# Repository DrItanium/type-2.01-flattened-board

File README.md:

This project is a flattening of my i960 Eurocard Bus design into a mini itx
motherboard. The idea is that by leveraging the mini-itx/atx ecosystem I will
save a bunch of money. In this design, the chipset is an adafruit grand central
m4 with ram being provided by a file on an SD card (dedicated SD channel +
an effective cache implementation works wonders to hide nearly all latency).

The grand central m4 is exposed out the io shield area. You will see the
evolution of many ideas and where it started from as well. 

I have two 4809 microcontrollers on board as well. They are titled ME and PIC. 

ME or Management Engine abstracts the details of how one handles memory
transactions made by the i960. It generates the 20MHz clock and runs in lock
step with the i960Sx as well. The chipset (GCM4) interacts with the ME to
satisfy these requests. The communication protocol between chipset and ME is
designed to allow the chipset to run completely independently of the ME without
running too fast or out of sync. The ME also uses its CCLs to reduce the number
of ICs required. This includes:

- Enabling data lines on request by chipset
- Fail signal detection (externally synchronized)
- Ready signal detection with external override
- Controlling the i960 reset line (Chipset, ME, and PIC all have to be ready
		before i960 is pulled out of reset). Pullups and an external inverter
		are used to make sure that the i960 will stay in reset until everything is
		ready. 

PIC or Programmable Interrupt Controller makes sure that one can invoke any of
the four exposed interrupt lines by the i960Sx in a consistent manner. A serial
communication channel is provided to allow the chipset to configure the PIC.
The general idea is that each CCL of the PIC is devoted to a separate interrupt
line. The first three interrupts (~INT0, INT1, INT2) are meant for dedicated
interrupts within the i960. The third interrupt (~INT3) is the lowest priority
and designed for the chipset. When the chipset needs to interrupt the i960, it
sends an ~INT3. This causes the i960 to query the chipset what kind of
interrupt it was (through MMIO) and then send an IAC message to trigger an
internal interrupt. 

The PIC has peripherals like timers and such that can be connected to the CCLs
to trigger interrupts. The chipset talks with the PIC through the serial
connection to setup these options via the event system.

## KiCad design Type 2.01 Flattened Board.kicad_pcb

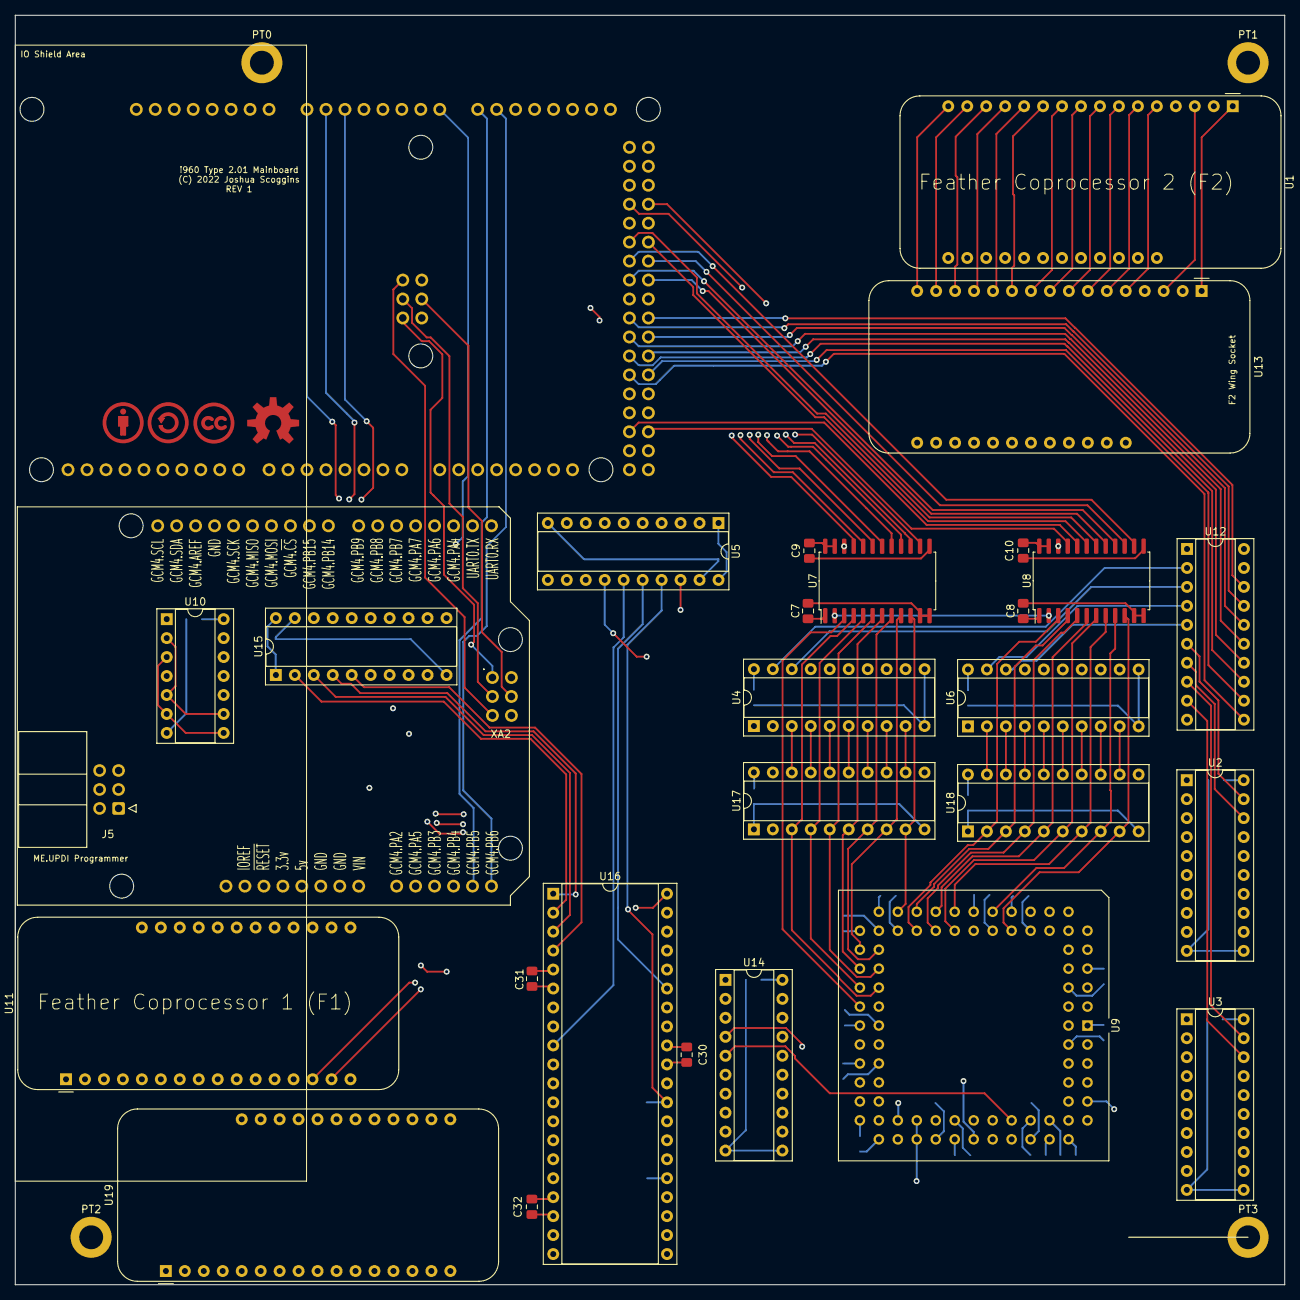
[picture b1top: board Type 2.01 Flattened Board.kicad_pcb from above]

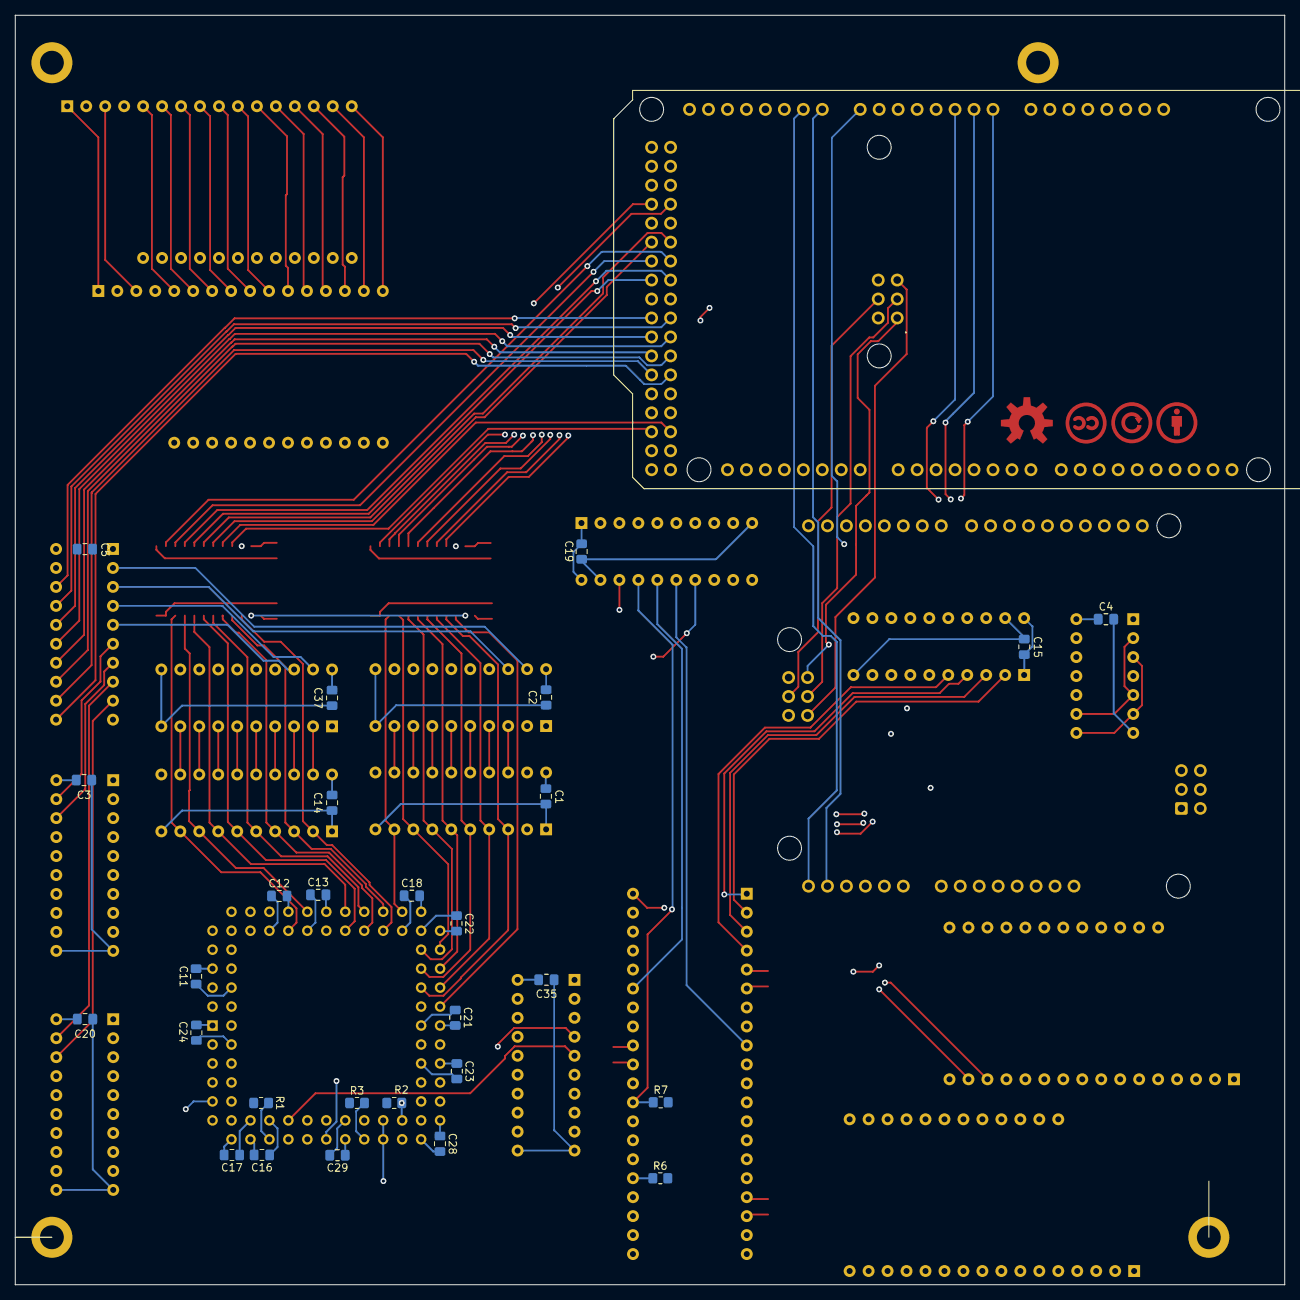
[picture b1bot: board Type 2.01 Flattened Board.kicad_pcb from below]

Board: 4 copper layers, 170.0 x 170.0 mm, 61 parts (29 on the bottom side), 209 nets.

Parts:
C1, C2, C3, C4, C5, C7, C8, C9, C10, C11, C12, C13, C14, C15, C16, C17, C18, C19, C20, C21, C22, C23, C24, C28, C29, C30, C31, C32, C35, C37: 0.1uF; C_0805_2012Metric_Pad1.18x1.45mm_HandSolder
J5: Conn_02x03_Odd_Even; IDC-Header_2x03_P2.54mm_Horizontal
PT0, PT1, PT2, PT3: MountingHole; MountingHole_3.2mm_M3_ISO14580_Pad
R1: 910; R_0805_2012Metric_Pad1.20x1.40mm_HandSolder
R2, R3, R6, R7: 10k; R_0805_2012Metric_Pad1.20x1.40mm_HandSolder
U1, U11, U13, U19: Adafruit_FeatherWing; Adafruit_Feather
U2, U3, U4, U6, U14: GAL16V8; DIP-20_W7.62mm_Socket
U5, U12, U15: 74AHC245; DIP-20_W7.62mm_Socket
U7, U8: 74LVC8T245; SOIC-24W_7.5x15.4mm_P1.27mm
U9: i960Sx_PLCC84; PLCC-84_THT-Socket
U10: 74AHC125; DIP-14_W7.62mm_Socket
U16: ATmega4809-PF; DIP-40_W15.24mm_Socket
U17, U18: 74AHC573; DIP-20_W7.62mm_Socket
XA1: Adafruit Grand Central M4; Arduino_Mega2560_Shield
XA2: Arduino_Uno_Shield

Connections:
+3.3V: U1.2 (3.3v), U1.28 (BAT), U11.2 (3.3v), U11.28 (BAT), U13.2 (3.3v), U13.28 (BAT), U19.2 (3.3v), U19.28 (BAT)
+3V3: XA1.3V3 (3.3V), XA2.3V3 (3.3V)
+5V: C1.1, C2.1, C3.1, C7.1, C8.1, C11.1, C12.1, C13.1, C14.1, C16.1, C17.1, C18.1, C19.1, C20.1, C21.1, C22.1, C23.1, C24.1, C28.1, C29.1, C30.1, C31.1, C32.1, C35.1, C37.1, J5.2, R1.2, R2.1, R3.1, R6.2, R7.2, U1.26 (USB), U2.20 (VCC), U3.20 (VCC), U4.20 (VCC), U5.1 (A->B), U5.20 (VCC), U6.20 (VCC), U7.1 (VCCA), U8.1 (VCCA), U9.1 (VCC), U9.6 (VCC), U9.17 (VCC), U9.21 (VCC), U9.31 (VCC), U9.33 (VCC), U9.44 (VCC), U9.47 (VCC), U9.53 (VCC), U9.62 (VCC), U9.71 (VCC), U9.73 (VCC), U11.26 (USB), U13.26 (USB), U14.20 (VCC), U16.5 (VCC), U16.17 (AVCC), U16.31 (VCC), U17.20 (VCC), U18.20 (VCC), U19.26 (USB), XA1.5V1 (5V), XA1.5V2 (SPI_5V), XA1.5V3 (5V), XA1.5V4 (5V), XA2.5V1 (5V), XA2.5V2 (SPI_5V)
/AREF: XA1.AREF, XA2.AREF
/BUS.PA2: XA1.A0, XA2.A0
/BUS.PA4: U1.10 (A5), U13.10 (A5), XA1.A13
/BUS.PA5: XA1.A1, XA2.A1
/BUS.PA6: U1.1 (~RESET), U13.1 (~RESET), XA1.A14
/BUS.PB2: U10.4, XA1.D9, XA2.D9
/BUS.PB3: XA1.A2, XA2.A2
/BUS.PB4: XA1.A7, XA2.A3
/BUS.PB5: XA1.A8, XA2.A4
/BUS.PB6: XA1.A9, XA2.A5
/BUS.PB7: U11.1 (~RESET), U19.1 (~RESET), XA1.A10
/BUS.PB8: U1.15 (TX), U13.15 (TX), XA1.A11
/BUS.PB9: U1.14 (RX), U13.14 (RX), XA1.A12
/BUS.PB18: U10.10, XA1.D8, XA2.D8
/BUS.PC18: XA1.D2 (D2_INT0), XA2.D2 (D2_INT0)
/BUS.PC19: XA1.D3 (D3_INT1), XA2.D3 (D3_INT1)
/BUS.PC20: XA1.D4, XA2.D4
/BUS.PC21: XA1.D5, XA2.D5
/BUS.PD20: XA1.D6, XA2.D6
/BUS.PD21: XA1.D7, XA2.D7
/DAZZLER.MISO: U10.2, U10.5, U10.9, XA2.D12
/Feather Copro0/Feather.A0: U11.5 (A0), U19.5 (A0)
/Feather Copro0/Feather.A1: U11.6 (A1), U19.6 (A1)
/Feather Copro0/Feather.A2: U11.7 (A2), U19.7 (A2)
/Feather Copro0/Feather.A3: U11.8 (A3), U19.8 (A3)
/Feather Copro0/Feather.A4: U11.9 (A4), U19.9 (A4)
/Feather Copro0/Feather.AREF: U11.3 (AREF), U19.3 (AREF)
/Feather Copro0/Feather.D5: U11.19 (D5), U19.19 (D5)
/Feather Copro0/Feather.D6: U11.20 (D6), U19.20 (D6)
/Feather Copro0/Feather.D9: U11.21 (D9), U19.21 (D9)
/Feather Copro0/Feather.D10: U11.22 (D10), U19.22 (D10)
/Feather Copro0/Feather.D11: U11.23 (D11), U19.23 (D11)
/Feather Copro0/Feather.D12: U11.24 (D12), U19.24 (D12)
/Feather Copro0/Feather.D13: U11.25 (D13), U19.25 (D13)
/Feather Copro0/Feather.EN: U11.27 (EN), U19.27 (EN)
/Feather Copro0/Feather.FREE: U11.16 (*), U19.16 (*)
/Feather Copro0/Feather.MISO: U11.13 (MISO), U19.13 (MISO)
/Feather Copro0/Feather.MOSI: U11.12 (MOSI), U19.12 (MOSI)
/Feather Copro0/Feather.SCK: U11.11 (SCK), U19.11 (SCK)
/Feather Copro0/Feather.SCL: U11.18 (SCL), U19.18 (SCL)
/Feather Copro0/Feather.SDA: U11.17 (SDA), U19.17 (SDA)
/Feather Copro1/Feather.A0: U1.5 (A0), U13.5 (A0)
/Feather Copro1/Feather.A1: U1.6 (A1), U13.6 (A1)
/Feather Copro1/Feather.A2: U1.7 (A2), U13.7 (A2)
/Feather Copro1/Feather.A3: U1.8 (A3), U13.8 (A3)
/Feather Copro1/Feather.A4: U1.9 (A4), U13.9 (A4)
/Feather Copro1/Feather.AREF: U1.3 (AREF), U13.3 (AREF)
/Feather Copro1/Feather.D5: U1.19 (D5), U13.19 (D5)
/Feather Copro1/Feather.D6: U1.20 (D6), U13.20 (D6)
/Feather Copro1/Feather.D9: U1.21 (D9), U13.21 (D9)
/Feather Copro1/Feather.D10: U1.22 (D10), U13.22 (D10)
/Feather Copro1/Feather.D11: U1.23 (D11), U13.23 (D11)
/Feather Copro1/Feather.D12: U1.24 (D12), U13.24 (D12)
/Feather Copro1/Feather.D13: U1.25 (D13), U13.25 (D13)
/Feather Copro1/Feather.EN: U1.27 (EN), U13.27 (EN)
/Feather Copro1/Feather.FREE: U1.16 (*), U13.16 (*)
/Feather Copro1/Feather.MISO: U1.13 (MISO), U13.13 (MISO)
/Feather Copro1/Feather.MOSI: U1.12 (MOSI), U13.12 (MOSI)
/Feather Copro1/Feather.SCK: U1.11 (SCK), U13.11 (SCK)
/Feather Copro1/Feather.SCL: U1.18 (SCL), U13.18 (SCL)
/Feather Copro1/Feather.SDA: U1.17 (SDA), U13.17 (SDA)
/GCM4.A0: U5.7 (A5), XA1.D39
/GCM4.A1: U5.8 (A6), XA1.D38
/GCM4.D0: U7.21 (B1), XA1.A3
/GCM4.D1: U7.20 (B2), XA1.A4
/GCM4.D2: U7.19 (B3), XA1.A5
/GCM4.D3: U7.18 (B4), XA1.A6
/GCM4.D4: U7.17 (B5), XA1.D48
/GCM4.D5: U7.16 (B6), XA1.D49
/GCM4.D6: U7.15 (B7), XA1.D46
/GCM4.D7: U7.14 (B8), XA1.D47
/GCM4.D8: U8.21 (B1), XA1.D25
/GCM4.D9: U8.20 (B2), XA1.D24
/GCM4.D10: U8.19 (B3), XA1.D45
/GCM4.D11: U8.18 (B4), XA1.D44
/GCM4.D12: U8.17 (B5), XA1.D41
/GCM4.D13: U8.16 (B6), XA1.D40
/GCM4.D14: U8.15 (B7), XA1.D43
/GCM4.D15: U8.14 (B8), XA1.D42
/GCM4.HLDA: U15.14 (B4), XA1.D17 (D17_RX2)
/GCM4.HOLD: U5.6 (A4), XA1.D26
/GCM4.L0: U12.18 (B0), XA1.D37
/GCM4.L1: U12.17 (B1), XA1.D36
/GCM4.L2: U12.16 (B2), XA1.D35
/GCM4.L3: U12.15 (B3), XA1.D34
/GCM4.L4: U12.14 (B4), XA1.D33
/GCM4.L5: U12.13 (B5), XA1.D32
/GCM4.L6: U12.12 (B6), XA1.D31
/GCM4.L7: U12.11 (B7), XA1.D30
/GCM4.~BE0: U15.13 (B5), XA1.D18 (D18_TX1)
/GCM4.~BE1: U15.12 (B6), XA1.D19 (D19_RX1)
/GCM4.~BOOT_SUCCESSFUL: U15.15 (B3), XA1.D16 (D16_TX2)
/GCM4.~BURST_LAST: U15.16 (B2), XA1.D10
/GCM4.~CHIPSET_BOOTED: U5.2 (A0), XA1.D29
/GCM4.~DO_CYCLE: U15.17 (B1), XA1.D11
/GCM4.~FEATHER_INT0: U11.10 (A5), U19.10 (A5), XA1.D13
/GCM4.~INTR0: U5.5 (A3), XA1.D22
/GCM4.~IN_TRANSACTION: U15.18 (B0), XA1.D12
/GCM4.~READY: U5.4 (A2), XA1.D23
/GCM4.~RESET960: U5.3 (A1), XA1.D27
/MISO: U10.3, U10.6, U10.8, XA1.D50
/MOSI: XA1.D51, XA2.D11
/SCK: XA1.D52, XA2.D13
/SCL: XA1.SCL, XA2.SCL
/SDA: XA1.SDA, XA2.SDA
/SPI_MISO: XA1.MISO (SPI_MISO), XA2.MISO (SPI_MISO)
/SPI_MOSI: XA1.MOSI (SPI_MOSI), XA2.MOSI (SPI_MOSI)
/SPI_SCK: XA1.SCK (SPI_SCK), XA2.SCK (SPI_SCK)
/UART0.RX: XA1.D0 (D0_RX0), XA2.D0 (D0_RX0)
/UART0.TX: XA1.D1 (D1_TX0), XA2.D1 (D1_TX0)
/UART3.RX: U11.15 (TX), U19.15 (TX), XA1.D15 (D15_RX3)
/UART3.TX: U11.14 (RX), U19.14 (RX), XA1.D14 (D14_TX3)
/VIN: XA1.VIN, XA2.VIN
/i960.A1: U4.3 (I3), U17.18 (Q1)
/i960.A2: U4.4 (I4), U17.17 (Q2)
/i960.A3: U4.5 (I5), U17.16 (Q3)
/i960.A4: U4.6 (I6), U17.15 (Q4)
/i960.A5: U4.7 (I7), U17.14 (Q5)
/i960.A6: U4.8 (I8), U17.13 (Q6)
/i960.A7: U4.9 (I9), U17.12 (Q7)
/i960.A8: U6.2 (I2), U18.19 (Q0)
/i960.A9: U6.3 (I3), U18.18 (Q1)
/i960.A10: U6.4 (I4), U18.17 (Q2)
/i960.A11: U6.5 (I5), U18.16 (Q3)
/i960.A12: U6.6 (I6), U18.15 (Q4)
/i960.A13: U6.7 (I7), U18.14 (Q5)
/i960.A14: U6.8 (I8), U18.13 (Q6)
/i960.A15: U6.9 (I9), U18.12 (Q7)
/i960.A16: U2.2 (I2), U9.16 (A16)
/i960.A17: U2.3 (I3), U9.15 (A17)
/i960.A18: U2.4 (I4), U9.14 (A18)
/i960.A19: U2.5 (I5), U9.13 (A19)
/i960.A20: U2.6 (I6), U9.12 (A20)
/i960.A21: U2.7 (I7), U9.11 (A21)
/i960.A22: U2.8 (I8), U9.10 (A22)
/i960.A23: U2.9 (I9), U9.9 (A23)
/i960.A24: U3.2 (I2), U9.8 (A24)
/i960.A25: U3.3 (I3), U9.5 (A25)
/i960.A26: U3.4 (I4), U9.4 (A26)
/i960.A27: U3.5 (I5), U9.3 (A27)
/i960.A28: U3.6 (I6), U9.83 (A28)
/i960.A29: U3.7 (I7), U9.82 (A29)
/i960.A30: U3.8 (I8), U9.81 (A30)
/i960.A31: U3.9 (I9), U9.80 (A31)
/i960.CLK: U14.1 (I1/CLK), U16.36 ((XDIR0/SCL/CCL0-OUT)PA3)
/i960.CLK2: U9.55 (CLK2), U16.40 ((XDIR0_ALT/CLKO/~SS)PA7)
/i960.D0: U7.3 (A1), U9.41 (D0)
/i960.D1: U7.4 (A2), U9.40 (AD1), U17.3 (D1)
/i960.D2: U7.5 (A3), U9.39 (AD2), U17.4 (D2)
/i960.D3: U7.6 (A4), U9.38 (AD3), U17.5 (D3)
/i960.D4: U7.7 (A5), U9.37 (AD4), U17.6 (D4)
/i960.D5: U7.8 (A6), U9.36 (AD5), U17.7 (D5)
/i960.D6: U7.9 (A7), U9.35 (AD6), U17.8 (D6)
/i960.D7: U7.10 (A8), U9.30 (AD7), U17.9 (D7)
/i960.D8: U8.3 (A1), U9.29 (AD8), U18.2 (D0)
/i960.D9: U8.4 (A2), U9.28 (AD9), U18.3 (D1)
/i960.D10: U8.5 (A3), U9.27 (AD10), U18.4 (D2)
/i960.D11: U8.6 (A4), U9.26 (AD11), U18.5 (D3)
/i960.D12: U8.7 (A5), U9.25 (AD12), U18.6 (D4)
/i960.D13: U8.8 (A6), U9.24 (AD13), U18.7 (D5)
/i960.D14: U8.9 (A7), U9.20 (AD14), U18.8 (D6)
/i960.D15: U8.10 (A8), U9.19 (AD15), U18.9 (D7)
/i960.DT\~R: U7.2 (DIR), U8.2 (DIR), U9.68 (DT\~R)
/i960.W\~R: U4.2 (I2), U9.66 (W\~R)
/i960.~BE0: U9.52 (~BE0), U14.3 (I3), U15.7 (A5)
/i960.~BE1: U9.51 (~BE1), U14.4 (I4), U15.8 (A6)
/i960.~DEN: U7.22 (~OE), U8.22 (~OE), U9.67 (~DEN), U16.28 ((AIN15)PF5)
/i960/5V_~CHIPSET_BOOTED: U5.18 (B0), U16.34 ((RXD0/CCL0-IN1)PA1)
/i960/5V_~READY: U5.16 (B2), U16.35 ((XCK0/SDA/CCL0-IN2)PA2)
/i960/5V_~RESET: R7.1, U5.17 (B1), U16.29 (PF6(~RESET))
/i960/ALE: U9.78 (ALE), U17.11 (Load), U18.11 (Load)
/i960/C0: U4.19 (IO1), U12.2 (A0)
/i960/C1: U4.18 (IO2), U12.3 (A1)
/i960/C2: U6.19 (IO1), U12.4 (A2)
/i960/C3: U6.18 (IO2), U12.5 (A3)
/i960/C4: U2.19 (IO1), U12.6 (A4)
/i960/C5: U2.18 (IO2), U12.7 (A5)
/i960/C6: U3.19 (IO1), U12.8 (A6)
/i960/C7: U3.18 (IO2), U12.9 (A7)
/i960/INT0_OUT: U14.2 (I2), U16.12 ((AIN3/CCL2-OUT)PD3)
/i960/READY_INTERMEDIATE: U14.6 (I6), U16.26 ((AIN13/XDIR2/CCL3-OUT)PF3)
/i960/SEL_A0: U2.12 (IO8), U3.12 (IO8), U4.12 (IO8), U5.13 (B5), U6.12 (IO8)
/i960/SEL_A1: U2.13 (IO7), U3.13 (IO7), U4.13 (IO7), U5.12 (B6), U6.13 (IO7)
/i960/UPDI: J5.1, U16.30 (UPDI)
/i960/UPDI_RXD: J5.4, U16.8 ((RXD1_ALT)PC5)
/i960/UPDI_TXD: J5.5, U16.7 ((TXD1_ALT)PC4)
/i960/i960.HLDA: U9.61 (HLDA), U15.6 (A4)
/i960/i960.HOLD: U5.14 (B4), U9.64 (HOLD)
/i960/i960.~BLAST: U9.69 (~BLAST\~FAIL), U14.5 (I5), U16.27 ((AIN14)PF4)
/i960/i960.~BOOT_SUCCESSFUL: U15.5 (A3), U16.4 ((XDIR1/~SS_ALT/CCL1-OUT)PC3)
/i960/i960.~BURST_LAST: U15.4 (A2), U16.1 ((TXD1/MOSI_ALT/CCL1-IN0)PC0)
/i960/i960.~DO_CYCLE: U15.3 (A1), U16.3 ((XCK1/SCK_ALT/CCL1-IN2)PC2)
/i960/i960.~INT0: R2.2, U9.57 (~INT0), U14.19 (IO1)
/i960/i960.~INT3: R3.2, U9.60 (~INT3)
/i960/i960.~IN_TRANSACTION: U15.2 (A0), U16.2 ((RXD1/MISO_ALT/CCL1-IN1)PC1)
/i960/i960.~LOCK: R1.1, U9.70 (~LOCK)
/i960/~CHIPSET_INT: U5.15 (B3), U16.9 ((AIN0/CCL2-IN0)PD0)
/i960/~ME_FAIL_IN: U14.18 (IO2), U16.33 ((CLKI/TXD0/CCL0-IN0)PA0)
/i960/~READY960: U9.79 (~READY), U14.17 (I03)
/i960/~RESET960: U9.56 (~RESET), U14.16 (IO4)
/i960/~RESET_INTERMEDIATE: R6.1, U14.7 (I7), U16.25 ((AIN12/XCK2/CCL3-IN2)PF2)
/~CS: U10.1, XA1.D53 (D53_SS), XA2.D10 (D10_CS)
/~RESET_{0}: XA1.RST1 (RESET), XA2.RST1 (RESET)
/~RESET_{1}: XA1.RST2 (SPI_RESET), XA2.RST2 (SPI_RESET)
GND: C1.2, C2.2, C3.2, C4.2, C5.2, C7.2, C8.2, C9.2, C10.2, C11.2, C12.2, C13.2, C14.2, C15.2, C16.2, C17.2, C18.2, C19.2, C20.2, C21.2, C22.2, C23.2, C24.2, C28.2, C29.2, C30.2, C31.2, C32.2, C35.2, C37.2, J5.6, U1.4 (GND), U2.10 (GND), U2.11 (I10/~OE), U3.10 (GND), U3.11 (I10/~OE), U4.10 (GND), U4.11 (I10/~OE), U5.10 (GND), U5.19 (CE), U6.10 (GND), U6.11 (I10/~OE), U7.11 (GND), U7.12 (GND), U7.13 (GND), U8.11 (GND), U8.12 (GND), U8.13 (GND), U9.7 (GND), U9.18 (GND), U9.22 (GND), U9.32 (GND), U9.34 (GND), U9.43 (GND), U9.48 (GND), U9.54 (GND), U9.58 (INT1), U9.59 (INT2), U9.63 (GND), U9.72 (GND), U9.74 (GND), U9.77 (GND), U9.84 (GND), U10.7 (GND), U11.4 (GND), U12.10 (GND), U12.19 (CE), U13.4 (GND), U14.10 (GND), U14.11 (I10/~OE), U15.10 (GND), U15.19 (CE), U16.6 (GND), U16.18 (GND), U16.32 (GND), U17.1 (OE), U17.10 (GND), U18.1 (OE), U18.10 (GND), U19.4 (GND), XA1.GND1 (GND), XA1.GND2 (GND), XA1.GND3 (GND), XA1.GND4 (SPI_GND), XA1.GND5 (GND), XA1.GND6 (GND), XA2.GND1 (GND), XA2.GND2 (GND), XA2.GND3 (GND), XA2.GND4 (SPI_GND)
VCCB: C4.1, C5.1, C9.1, C10.1, C15.1, U7.23 (VCCB), U7.24 (VCCB), U8.23 (VCCB), U8.24 (VCCB), U10.14 (VCC), U12.1 (A->B), U12.20 (VCC), U15.1 (A->B), U15.20 (VCC), XA1.IORF (IOREF), XA2.IORF (IOREF)

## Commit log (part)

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2022-05-12 Start defining the pinout of the grand central m4
2022-05-12 More bus pin out action
2022-05-12 Got the bus pinout done
2022-05-12 Fix up analog pinout so that reading and writing data lines is as efficient as possible
    It does require using some of the analog pins that would be found in the
    uno section. Just use some of the other analog pins found in the
    extended set instead.
2022-05-13 Added CCL connections as text
2022-05-13 Got the address muxer finished
2022-05-13 Use bus lines for logic level conversion
2022-05-13 Added an i960 sheet
2022-05-13 Update everything and keep laying out the i960 features
    Use bus wires as much as possible
2022-05-13 Put the management engine into the i960 sheet
    It will be responsible for generating the 20mhz clock. However, the
    interrupts probably need to be handled externally by another processor
    to make sure we don't bog down the management engine.
2022-05-13 USE HC158/AHC158s to allow me to change the aux hardware on this board
    The issue I'm seeing is that this board is very complex and I need a way
    to fix bugs without adding a lot of strange garbage. My plan is to move
    the management engine and various parts onto a board that is plugged
    into the main board. The other way I could do it is provide this
    capability but use multiplexer chips to select the source. That way it
    can work without this. Plus I can still fix bugs in the future.
2022-05-14 Use AHC244s instead of AHC158s for the address lines
    Makes it much easier to design the selection bus!
2022-05-14 Start defining the components needed for keeping track of the address and data lines
2022-05-14 Instead of using a double buffer design, just connect the bus selector and DEN lines together with an or gate.
    That way we keep the transceivers off of the bus.
2022-05-14 Use an AHC138/HC138 for decoding the fail circuit
    It is much simpler this way. I can also use the other states to define
    the actions to perform.
2022-05-14 Make the management engine responsible for handling reset capabilities
    My idea is to use the event system to route the ME_Booted pin to a ccl
    within the me to complete the package.
    The output of this ccl will be RESET960 and that can be handled manually
    until we get the CCLs up. Then we can wait until all the parts have
    started up. Hell we can use an AHC138 for this as well!
2022-05-14 Use the Management Engine for the reset controller.
    It becomes much easier to work around logic bugs with the CCL. I just
    setup PF0 as an output but wire that to CCL3.EVTA (I do this for the
    10MHz signal tests where I routed PA7 as a event source)
    So that allows me to control the CCL that way. If that fails then I can
    just do polling on boot with no problems.
    I also added pullups to make sure that on a reset from the chipset we
2022-05-14 Integrate the 10MHz signal generator into the Management Engine
    Makes it much easier to control things
2022-05-14 Fix a screwup for labels
2022-05-14 Use an AHC174 to handle teh fail sync
    I realized that we can just pass the sync'd result without doing an
    invert at all. It means that I can easily resolve the logic in the
    management engine without shenanigans!
    I am also thinking that it provides a better ready signal sync backup
    than the external device. I can just reroute it easily
2022-05-14 Use an inverter and and-gate combo with the hex flip flop
2022-05-14 Added GCM4 bus concept to simplify exposing connections to the i960
2022-05-15 Part assignment
2022-05-15 Move extraneous signals to register 4
2022-05-15 Added the LOW global label
    Simplify things
2022-05-15 Added the updi connectors
2022-05-15 use the output enable lines on the latches and buffers to do direct logic level conversion
    Save some chips in the process.
2022-05-15 Do a bulk update and fix all values
2022-05-15 Use individual resistors for better layout purposes
2022-05-15 Connect LOCK and AS to the management engine
    Don't do a breakout!
2022-05-15 Use a third 4809 running independently to act as glue and startup unit.
    I was able to remove a nor gate ic by adding. I am also planning to use
    the CCLs for other features as well. Perhaps as a simpler inverter.
2022-05-15 Added a communication channel between the different glue chips.
    I am considering connecting this up to the chipset through glue
2022-05-15 Use GLUE to setup a query network. I want to make sure that we can talk to the different chips as easily as possible.
2022-05-16 Put the interrupt lines back
2022-05-16 Update the pinout and use levels of abstraction
2022-05-16 Make sure we can mask interrupts externally and also make the serial connections to each device a separate thing.
2022-05-16 Just use the communication channels without XCK
2022-05-16 Pinout related actions
2022-05-16 layout troubles
    I think I need to step back and simplify things.
    Having the uno connector on board doesn't actually make that much sense
    to be honest. I'm going to drop it out
2022-05-16 Drop the AHC138
    We don't need it anymore
2022-05-17 Update the pinout to only use ports A and B
2022-05-19 Chipset only gets access to ~INT3 by default
    Use the other interrupts for peripherals on the PIC.
2022-05-19 Save an AHC245 by reducing the number of interrupts accessible by the chipset
2022-05-19 Drop the external connector for overriding.
    I think I'm just going to add the two synchronizers as a backup but put
    the edge detection logic into the CCL as the backup
2022-05-19 Added the jumper block
2022-05-19 More pullup and pulldown resistors
2022-05-19 Use an AHC157 for the deactivation of the interrupt lines while changes are being made to the CCLs
    Instead of using tons of pullups and downs, use the AHC157 channel
    feature. Channel 0 is the connection between CCLS and i960. Channel 1 is
    a fixed pattern that is useful for booting and deactivating all
    interrupts
2022-05-19 Added the CC BY-SA 3.0 license
2022-05-19 Do CC SA-BY 4.0 instead
2022-05-19 Added some documentation as to why the ahc157 was used
2022-05-19 Fix legit warnings and do more part selection
2022-05-19 Update the AHC138 to have the following pattern:
    High bits to Low bits
    Bit 2) W/~{R}
    Bit 1) ~{BE0}
    Bit 0) ~{BE1}
    The byte enable bits are reversed to make the output easier brain out
    since they are active low.
2022-05-19 Added extra resistor pack for missing pullup part
2022-05-19 Use multiple resistor packs to simplify the design further
2022-05-21 Added feather and uno connector!
2022-05-21 Drop the feather wing connector
    My idea is to use two gcm4's for this instead.
    It is a much better setup because the second GCM4 is a perfect use of
    the free communication channels
2022-05-21 Add a second grand central M4 for linkage work
2022-05-21 Added both feather wing coprocessor sockets
2022-05-21 Wire up more components
2022-05-21 Replace the AHC245s with four AHC157s to simplify the design
2022-05-21 Define the muxer in terms of A0-A15
2022-05-21 Keep laying stuff out
2022-05-21 Do the research into an 8-bit address bus
    Started routing as well.
2022-05-21 Design simplification
2022-05-22 More pcb layout changes
2022-05-22 eliminate an inverter by not exposing the 10 and 20mhz clock to the VCC domain
    It isn't being used anywhere!
2022-05-22 Drop an AHC74 and two resistor packs
    Add an AHC174 in its place. This is for the edge detector. It should now
    be far simpler to route this compared to an AHC74
2022-05-22 Added feather interrupts as well
2022-05-22 Clean up feather terminal connections and add an interrupt line back to chipset
    It allows me to interrupt the chipset to perform some sort of action
2022-05-22 Proper part selection
2022-05-22 Better layout :)
    NEed to add a feather breakout as the final part
2022-05-22 Make sure grouping is right
2022-05-22 Added a new 9 pin breakout header for me pins
    PORTA on the ME is now free. CLK is now connected to PD7. That way I can
    reuse all of PORTA for whatever I want in the future.
2022-05-22 Added an RTC socket
2022-05-23 Drop the HC125 and start redoing the pinout for the management engine to maximize layout capabilities
2022-05-23 Fix grouping
2022-05-23 Get rid of ME_BOOTED because it is no longer necessary with the reset circuit no longer handled by a CCL.
    Turns out to be a massive waste that way otherwise.
2022-05-23 Increased simplicity
2022-05-24 Breakout all unused pins from the management engine
2022-05-24 Start routing
2022-05-24 More lines being routed. Looks pretty clean so far
2022-05-25 More layout fixes and bug fixes
2022-05-25 More layout changes
    Most importantly, move the ~{AS} and CLK,CLK2 pins to separate breakout
    headers
2022-05-25 More trace layouts
2022-05-25 More traces laid out
2022-05-26 More routing and adding of some keepouts
2022-05-26 Added the fill areas but not having it filled in right now
2022-05-26 More final routings
2022-05-26 More layout connections
2022-05-26 More power pin updates
2022-05-26 Added some text markers to the board
2022-05-26 Added pinout labelling
2022-05-27 Initial design fully laid out.
    Still need to add more text
2022-05-27 Added some extra marks
2022-05-27 Breakout the two unconnected pins from the gcm4
2022-06-20 Fix naming + more features
2022-07-04 Move all components around and group them as needed on the PCB
2022-07-04 Move Feather coprocessors to a separate sheet to make it easy to duplicate
2022-07-04 Use a gal instead of the ahc157 and ahc04
2022-07-04 Adding a 16-to-8 muxer
    Realized that if I use two layers of AHC158s then it will handle
    inverting for me :)!
2022-07-04 Drop the PIC and only have one interrupt line
    Move the FAIL circuit to the GAL as I have a working implementation for
    that as well!
2022-07-04 Rearrange pinout of me to make routing easier
2022-07-04 Even more simplification and be able to reset feathers separately from the chipset
    Makes it possible to also reset them if needed as well
2022-07-04 Try doing proper proper pcb layout... still too complex
    I want to use some gals to do 8->2 conversion
2022-07-05 Better board layout using the GAL chips
2022-07-05 Use a layout reminiscent of the serialized versions of the i960 for chip layouts
2022-07-05 Drop the number of feather co processors down to 1
    The dazzler provides audio and video so the only thing left would be
    around bluetooth or something similar
2022-07-05 Only have one feather
    Also came up with a good layout in the form of a "card" style that can
    easily be moved around for the i960
2022-07-05 Do the majority of the routing
    Drop the i960 header breakout, also don't connect LOCK to the management
    engine. I have no idea what it would be useful for. The chipset is the
    only thing that will directly interact with the i960 so locking isn't
    necessary.
2022-07-05 make sure that we actually don't connect the lock pin
2022-07-05 Added feather wing sockets next to each plug
    F1 has its battery connector blocked by the dazzler shield.
    This is not that big of a deal to be honest.
2022-07-05 Nearly finished!
2022-07-05 Fix up an issue with 3.3v vs 3v3 power planes
    Also, link up more power pads to corresponding power plane
2022-07-05 Added labels for everything so I don't need to keep referring back to any sort of bill of materials
2022-07-09 Added a breakout of the management engine pins
2022-07-09 Finished adding text

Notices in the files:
Type 2.01 Flattened Board.kicad_pcb:
(C) 2022 Joshua Scoggins
